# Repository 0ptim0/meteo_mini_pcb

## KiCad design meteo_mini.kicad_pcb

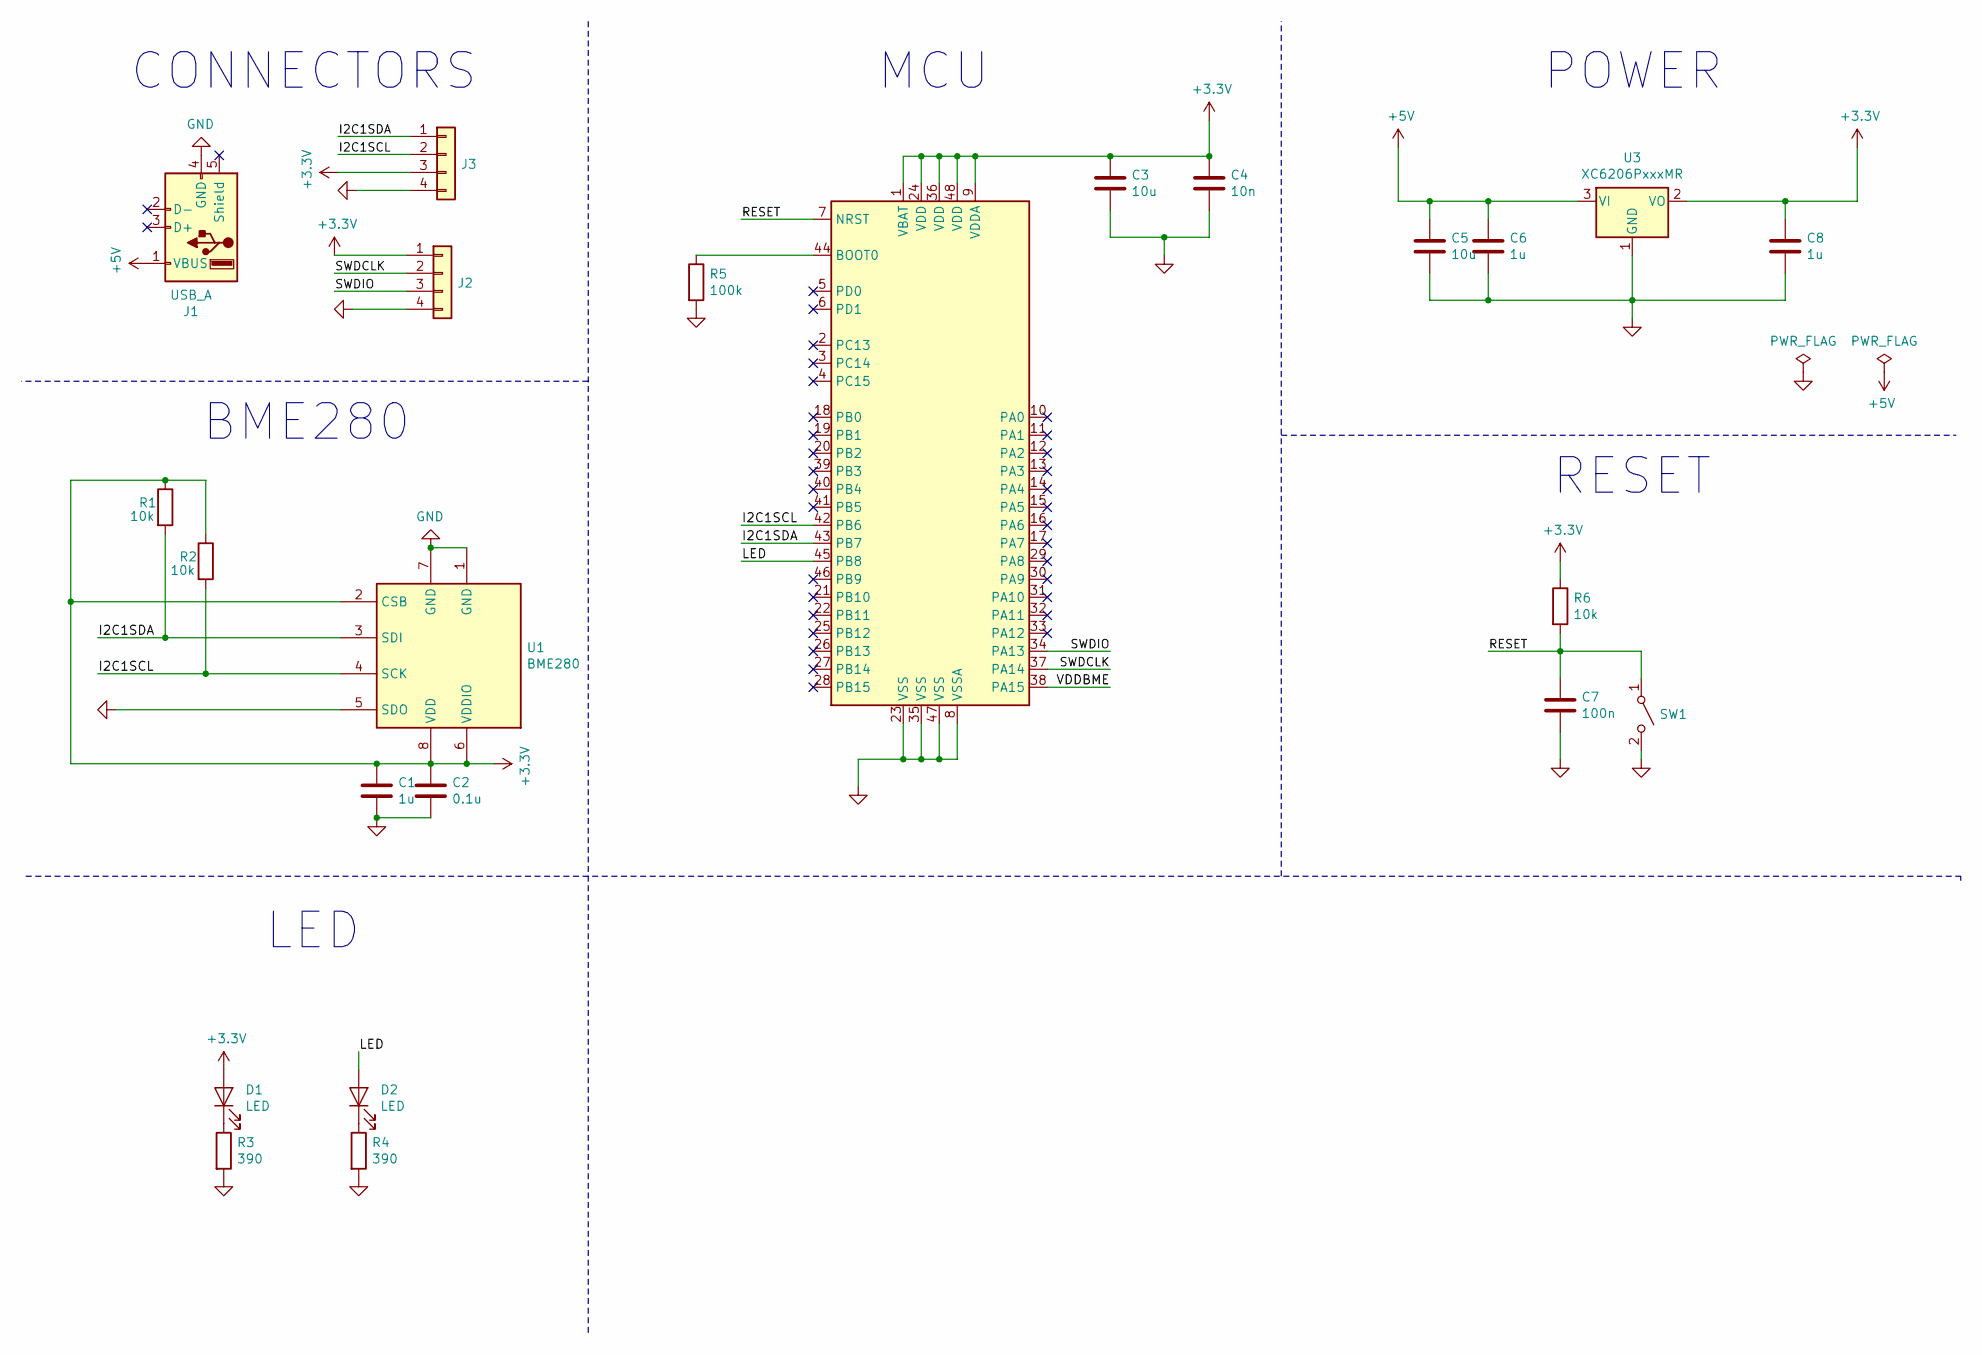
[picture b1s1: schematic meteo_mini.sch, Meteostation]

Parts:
C1, C6, C8: 1u; C_0603_1608Metric
C2: 0.1u; C_0603_1608Metric
C3, C5: 10u; C_0603_1608Metric
C4: 10n; C_0603_1608Metric
C7: 100n; C_0603_1608Metric
D1, D2: LED; LED_0603_1608Metric
J1: USB_A; USB_A_CNCTech_1001-011-01101_Horizontal
J2, J3: Conn_01x04; PinHeader_1x04_P2.54mm_Vertical
R1, R2, R6: 10k; R_0603_1608Metric
R3, R4: 390; R_0603_1608Metric
R5: 100k; R_0603_1608Metric
SW1: SW_SPST; SW_SPST_FSMSM
U1: BME280; Bosch_LGA-8_2.5x2.5mm_P0.65mm_ClockwisePinNumbering
U2: STM32F103C8T6; LQFP-48_7x7mm_P0.5mm
U3: XC6206PxxxMR; SOT-23

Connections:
+3V3: C1.1, C2.1, C3.1, C4.1, C8.1, D1.2 (A), J2.1, J3.3, R1.1, R2.1, R6.1, U1.2 (CSB), U1.6 (VDDIO), U1.8 (VDD), U2.1 (VBAT), U2.9 (VDDA), U2.24 (VDD), U2.36 (VDD), U2.48 (VDD), U3.2 (VO)
+5V: C5.1, C6.1, J1.1 (VBUS), U3.3 (VI)
/I2C1SCL: J3.2, R2.2, U1.4 (SCK), U2.42 (PB6)
/I2C1SDA: J3.1, R1.2, U1.3 (SDI), U2.43 (PB7)
/LED: D2.2 (A), U2.45 (PB8)
/RESET: C7.1, R6.2, SW1.1 (A), U2.7 (NRST)
/SWDCLK: J2.2, U2.37 (PA14)
/SWDIO: J2.3, U2.34 (PA13)
/VDDBME: U2.38 (PA15)
GND: C1.2, C2.2, C3.2, C4.2, C5.2, C6.2, C7.2, C8.2, J1.4 (GND), J2.4, J3.4, R3.2, R4.2, R5.2, SW1.2 (B), U1.1 (GND), U1.5 (SDO), U1.7 (GND), U2.8 (VSSA), U2.23 (VSS), U2.35 (VSS), U2.47 (VSS), U3.1 (GND)
unnamed: D1.1 (K), R3.1
unnamed: D2.1 (K), R4.1
unnamed: R5.1, U2.44 (BOOT0)

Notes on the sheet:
POWER
RESET
CONNECTORS
MCU
BME280
LED

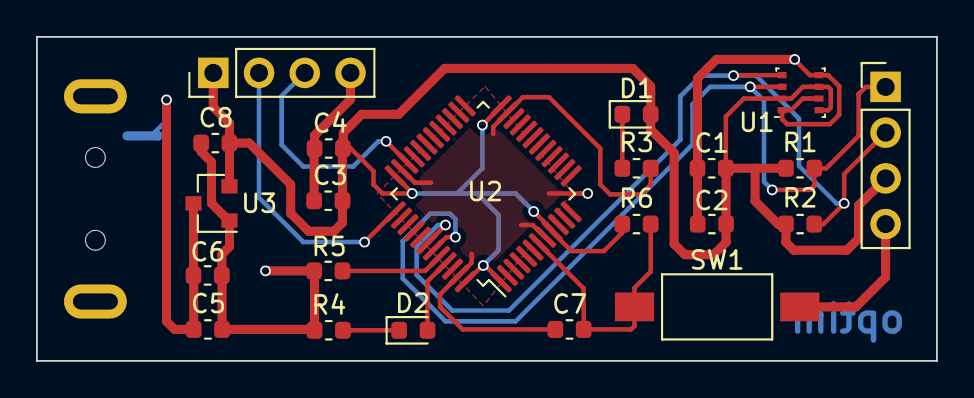
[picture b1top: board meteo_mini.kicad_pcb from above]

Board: 2 copper layers, 50.0 x 18.0 mm, 23 parts (1 on the bottom side), 12 nets.

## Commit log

2021-03-05 added pcb project in git
2021-03-05 added screenshots
2021-03-20 new pcb design is coming
2021-06-15 Move components
2021-06-15 First version
2021-06-16 Ground polygone under MCU, Vcc though via
2021-06-16 New PCB production
2021-06-16 update gerber files
